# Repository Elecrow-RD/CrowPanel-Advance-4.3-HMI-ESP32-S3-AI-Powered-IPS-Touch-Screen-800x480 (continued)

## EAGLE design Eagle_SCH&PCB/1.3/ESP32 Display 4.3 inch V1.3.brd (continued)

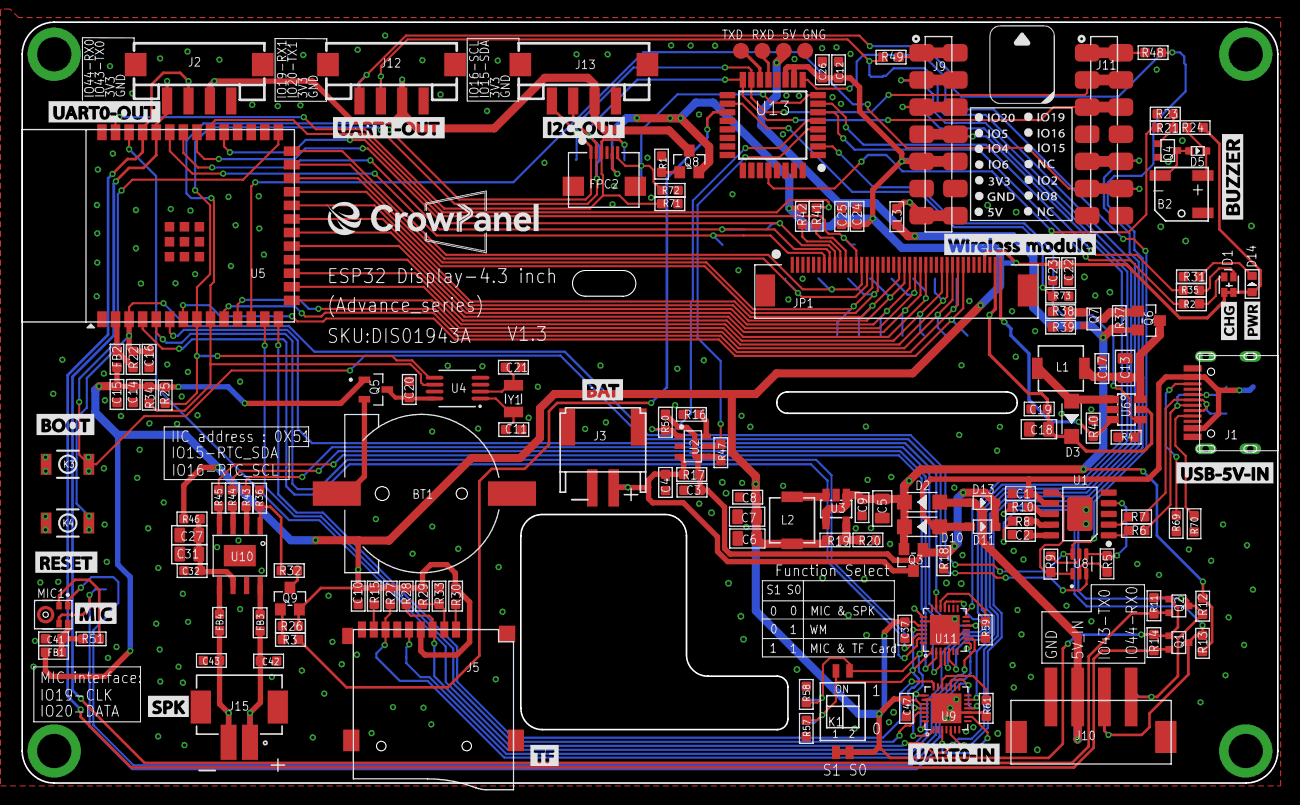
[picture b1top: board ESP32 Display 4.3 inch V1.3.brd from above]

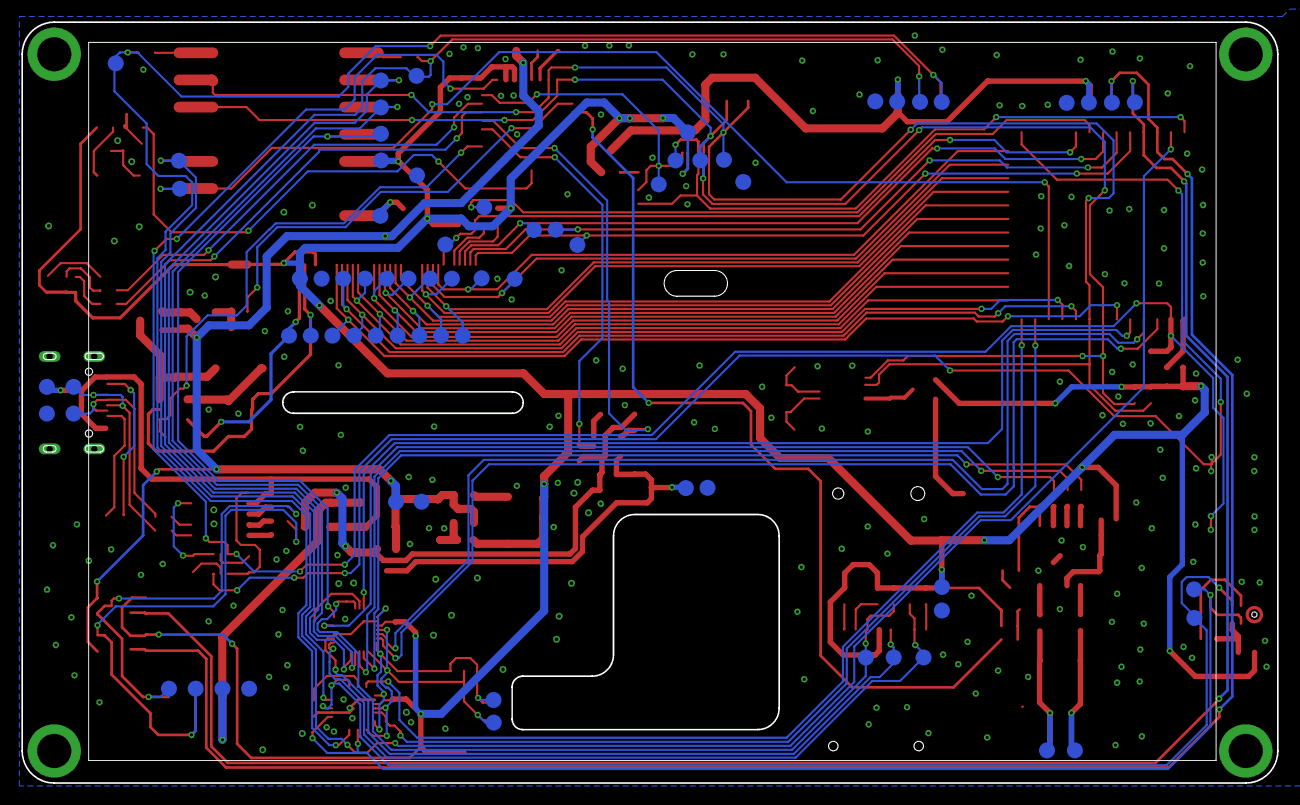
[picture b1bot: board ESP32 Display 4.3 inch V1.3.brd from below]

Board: 2 copper layers, 117.5 x 71.2 mm, 224 parts (71 on the bottom side), 127 nets.

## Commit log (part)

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2026-04-22 sync example/V1.1V1.2
2026-06-03 libraries
2026-06-10 esp32
2026-06-15 rename folders
2026-06-24 Thread
